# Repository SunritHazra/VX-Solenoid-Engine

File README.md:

# VX Solenoid Engine — V2 Solenoid Engine

The project *"V2 Solenoid Engine"* is the second project of the long-term vision of "VX Solenoid Engine", which aims to build progressive solenoid engines with real engineering and proper planning. I have designed and completed the V1 Solenoid Engine before which was the prototype (you can find this in the first journal entry), and I had a partially designed a V10 Solenoid Engine with the help of an engineer from the United Kingdom (UK).

The V2 Solenoid Engine is a custom-designed electromechanical engine that converts electrical energy into rotational mechanical motion using electromagnetic actuation. Instead of combustion, the engine uses solenoids to generate magnetic fields that pull ferromagnetic plungers inside cylindrical sleeves, producing linear motion. This motion is transferred through a yoke and crankshaft mechanism that converts the linear movement into continuous rotation, similar to the working principle of a traditional piston engine.

This project is made with the aim of creating an engine that works efficiently, consistently and with coolness (not talking about thermal coolness), wirelessly. The ESP32 allows the user to run the engine at any speed, control the firing, etcetera. The engine is intended to be controllable through a laptop, a phone or any device wirelessly.

<center>
  
</center>

We can often see solenoid engines nowadays as hobby toys, on platforms like YouTube, so what separates this project from those?  
Well, this has a PCB, MOSFET switching based on IR sensors, and it is made with performance and efficiency in mind. Please note that, efficiency is not the goal of this project, and this is an experimental setup to study electromagnetic actuation.

---

## Project Overview

The entire mechanical system is designed in **Autodesk Fusion** and the PCBA was designed in **KiCad**, with structural components and mechanical components (except flywheel) intended for MJF and SLS 3D printing, while control electronics are built around an ESP32-DEVKIT-V1 featuring ESP32-WROOM-32 and TCRT5000 IR position sensing. The engine is powered by a Mean Well LRS-450-24, that gives an output of 24 volts and 18.8 amperes.

The current design features a two-cylinder (V2) configuration sharing a single crankshaft, firing at 180 degrees, which improves rotational balance and reduces dead zones during operation. To control the engine’s timing, infrared reflective sensors monitor the position of the crankshaft and provide feedback to an ESP32 microcontroller, which determines when each solenoid should be energized (when the power should be on). A custom PCB handles the electronics (except the SMPS) required for switching the high-current solenoid coils, integrating MOSFET drivers, power regulation, and sensor interfaces while separating high-power and low-voltage logic systems for stability.

The PCB has two different power inputs: one inputs 5V from a battery and one inputs 24V from the Mean Well LRS-450-24 (18.8 A). There are four more logical inputs (screw terminals): Two (4 pins) for each of the IR Sensor, for A, CATH, COLL and E. And there are two big output screw terminals, for each solenoid.

The PCB has no traces for the components through which 18.8 A flows. So, they have to be soldered pin-to-pin manually with thick wire suitable for that current like 18 AWG. I did this as I didn't want to make the traces too thick, probable to overheating and for safety reasons. And of course, I didn't want to use 2 oz thickness as it is expensive.

Together, the mechanical structure, sensing system, embedded controller, and power electronics form a programmable electromagnetic engine platform that allows experimentation with firing timing, control strategies, and electromechanical system design.

The engine demonstrates:
* Electromagnetic actuation
* Crankshaft-based mechanical power conversion
* Embedded timing control
* Hybrid manufacturing (3D printing + CNC)
* MOSFET Switching

**Note:** The flywheel has to be as heavy as possible, so it is better to CNC machine it despite the cost. A large flywheel is used to stabilize rotational inertia and maintain smooth motion between electromagnetic pulses.

---

## Core Concept

A solenoid is an electromechanical device that generates a magnetic field when current flows through its copper coil. A ferromagnetic plunger inside the solenoid is pulled toward the coil center. I just doubled it so that it looks more cool, and is more loud (really).

In this engine, this is what happens fundamentally:
1. A microcontroller (ESP32) activates the solenoid coil based on the position of the crank
2. Magnetic force pulls the ferromagnetic soft iron plunger
3. The plunger drives the connecting rod connected to the crankshaft
4. The crankshaft rotates
5. A flywheel smooths rotational motion
6. IR sensors detect crank position
7. The controller switches coils again

This cycle produces **continuous rotation**, with two pistons firing periodically at 180 degrees.

---

## Key Features

### Multi-Cylinder Mechanical Layout
The engine uses a **V2 configuration**, where two solenoid-driven cylinders operate on a shared crankshaft. This arrangement improves balance and reduces rotational dead zones, allowing smoother and more continuous motion.

### Electromagnetic Actuation
Each cylinder converts electrical energy into linear mechanical motion.  
Each cylinder contains:
* Copper coil winding
* Ferromagnetic plunger
* Linear motion sleeve

When current flows through the coil, a magnetic field is generated that pulls the plunger inward. The plunger’s movement converts magnetic attraction into controlled mechanical displacement.

### Crankshaft Mechanism
The crankshaft converts the linear motion of the plungers into rotational motion.  
Main components include:
* Crank pins
* Yokes
* Connecting linkages

The crankshaft geometry is intentionally compact and shortened to reduce friction losses and improve overall mechanical efficiency.

### Flywheel Stabilization
A large flywheel is mounted on the crankshaft to stabilize rotation.  
Its functions include:
* Increasing rotational inertia
* Reducing stalling between solenoid pulses
* Smoothing torque output

The flywheel helps maintain continuous rotation even when the solenoids are not actively pulling the plungers.

### Optical Position Sensing
The engine uses TCRT5000 infrared reflective sensors to detect crankshaft position.  
These sensors allow the control system to:
* Identify the rotational phase of the crankshaft
* Trigger solenoids at the correct timing
* Prevent mistimed coil activation

This sensing system transforms the engine from a passive mechanism into an actively controlled electromechanical system.

### Exoskeleton Structural Frame
The engine is supported by a rigid exoskeleton frame that holds the mechanical system together. The frame:
* Maintains alignment of cylinders
* Supports bearings and shaft components
* Prevents structural flexing
* Provides mounting points for sensors and electronics

The exoskeleton also allows modular modifications and easier maintenance.

---

## Mechanical Design

The mechanical system consists of several interacting components that convert electromagnetic actuation into rotational motion.

**Solenoid Cylinder Assembly**  
Each cylinder assembly contains:
* Coil housing
* Copper winding space
* Plunger sleeve
* Linear motion channel

The sleeve guides the plunger along a fixed path and ensures proper alignment during motion.

**Yoke Mechanism**  
The yoke connects the plunger to the crankshaft and transfers the linear motion.  
The yoke geometry was thickened to:
* Increase structural strength
* Provide sufficient space for coil windings
* Reduce mechanical deformation during operation

**Crankshaft**  
The crankshaft assembly includes:
* Crank throws
* Bearing supports
* Shaft core
* Flywheel mount

The crank geometry was designed to minimize rotational inertia and reduce mechanical drag.

**Structural Frame**  
The outer frame forms a rigid skeleton that supports the entire mechanical system.  
It provides mounting locations for:
* Cylinder assemblies
* Sensor placements
* Bearing supports
* Crankshaft alignment

---

## Electronics Architecture

The electronics system coordinates solenoid activation and processes sensor input.

**Microcontroller**  
The engine uses an ESP32 DevKit V1 microcontroller.  
Responsibilities include:
* Reading sensor signals
* Determining crankshaft position
* Controlling solenoid activation timing
* Executing control logic

The microcontroller also enables future expansions such as telemetry and advanced control algorithms.

**Position Sensors**  
Crankshaft position is detected using TCRT5000 IR reflective sensors.  
These sensors detect reflective markers attached to the rotating assembly and provide feedback necessary for correct timing of solenoid activation.

**Power System**  
The solenoid coils require high-current switching.  
The typical power architecture includes:
* 24 V power supply
* MOSFET switching stage
* Flyback protection diodes
* Capacitor banks for current stabilization

These components allow safe and efficient control of the solenoid currents.

---

## Manufacturing Plan

The project uses a hybrid fabrication approach, combining additive manufacturing with CNC machining, to balance cost and quality.

**3D Printed Components**  
Most structural components are designed for 3D printing, including:
* Engine frame
* Coil housings
* Yokes
* Sensor mounts
* Structural supports

Likely materials include:
* PLA for early prototyping
* PETG or ABS for stronger functional parts

**CNC Machined Components**  
Precision mechanical parts are planned to be manufactured using CNC machining, primarily through JLCMC.  
These parts include:
* Crankshaft
* Metal shafts
* Mechanical fasteners
* Possibly the flywheel

CNC machining provides better tolerances, strength, and durability for rotating components.

---

## Bill of Materials

A complete bill of materials is provided in **BOM.csv**.  
**Note:** Cart screenshots for Amazon, JLC, and Robu have been added in the design review already. Certain parts are sourced locally and paid for by the creator. Therefore, it is not possible to provide links for those items, and their costs are not included in the BOM requested from HCB.

---

## Firmware

Firmware source code is located at:  
**Firmware/V2 Solenoid Engine Firmware.cpp**

To flash the firmware:
1. Install the Arduino IDE.
2. Install the ESP32 board package.
3. Open the firmware file.
4. Select the correct ESP32 board and port.
5. Upload the firmware to the microcontroller.

After flashing, disconnect USB if powering externally.  
(For PlatformIO users: platformio.ini is included in the firmware folder.)

---

## Wiring

The full wiring schematic is provided here:  
**Media/V2 Solenoid Engine Schematic and Wiring.pdf**

**External Wiring Summary**  
Mean Well LRS-450-24 (+24V/GND) ─── 18 AWG Red/Black ─── J1 on PCB  
Solenoid + connected to +24V rail  
Solenoid - connected to MOSFET drains (manual 18 AWG)  
TCRT5000 sensors connected to their 4-pin headers (A, CATH, COLL, E) → GPIO34/35  
NTC thermistor connected to GPIO36  

**One very important note (again):** The PCB has no traces for the components through which 18.8 A flows. So, they have to be soldered pin-to-pin manually with thick wire suitable for that current like 18 AWG. I did this as I didn't want to make the traces too thick, probable to overheating and for safety reasons. And of course, I didn't want to use 2 oz thickness as it is expensive.

---

## Assembly and Operation Guide

This guide explains how to assemble, wire, and operate the V2 Solenoid Engine after printing the mechanical parts and manufacturing the PCB. Read the entire document before starting assembly.  
Please note that this guide is not completely reliable as the engine is not manufactured and assembled (as of March, 2026).

**Safety Information**  
This project uses 24V DC power, 18.8 A and contains fast moving mechanical parts.  
Follow these obvious precautions:  
- Never power the system while assembling the mechanical structure.  
- Keep fingers, hair, and loose clothing away from the crankshaft and flywheel while running.  
- Always use a regulated 24V power supply capable of supplying adequate current.  
- Ensure correct polarity when connecting the power supply.  
- Disconnect power immediately if components become excessively hot or behave unexpectedly.  
- Do not run the engine unattended.

**Required Components**  
All required components are listed in the Bill of Materials:  
**Bill of Materials/V2 Bill of Materials.csv**

**Tools Required**  
Typical tools required for assembly include:  
- Hex keys / Allen keys  
- Screwdrivers  
- Small wrench or socket set  
- Soldering iron (if assembling PCB manually)  
- Wire cutters and strippers  
- Threadlocker (recommended for high-vibration components)

**Mechanical Assembly**  
Follow these general steps to assemble the mechanical structure.  
#### 1. Frame Assembly  
- Assemble the main frame using the 3D printed structural parts.  
- Secure all frame pieces using the specified fasteners from the BOM.  
- Ensure the frame is rigid and square.  

#### 2. Crankshaft and Flywheel  
- Install the crankshaft into the frame supports.  
- Attach the flywheel to the crankshaft.  
- Verify that the shaft rotates freely with minimal friction.  

#### 3. Piston and Connecting Rod  
- Attach the connecting rod to the crankshaft.  
- Install the piston assembly.  
- Ensure the piston moves smoothly through its full range of motion.  

#### 4. Solenoid Mounting  
- Mount the solenoid in the designated bracket.  
- Align the solenoid plunger with the piston linkage.  
- Ensure the plunger moves freely and does not bind.  

#### 5. Final Mechanical Check  
- Rotate the crankshaft manually.  
- Confirm the full mechanism moves smoothly.  
- Verify that no parts collide or rub excessively.  

**PCB Installation**  
The PCB design files are located in:  
**PCBA/**  
Files included:  
- KiCad project  
- PCB layout  
- schematic  
- gerbers  
- STEP model  

**PCB Mounting**  
- Secure the PCB to the frame using the provided mounting holes.  
- Ensure the board is isolated from metal surfaces if necessary.  
- Maintain airflow around the board for cooling.  

---

## Operation

After the engine is fully assembled and wired:  
1. Ensure the crankshaft rotates freely.  
2. Verify all wiring connections.  
3. Connect the 24V power supply.  
4. Power the system.  

The firmware will drive the solenoid according to the programmed timing, causing the piston to actuate and rotate the crankshaft.  
The flywheel stabilizes the rotation and maintains momentum between solenoid pulses.

---

## Expected Behavior

When operating correctly:  
- The engine should begin rotating shortly after power is applied.  
- The flywheel should maintain smooth rotational motion.  
- The solenoid should actuate in synchronization with the crankshaft motion.  

Performance depends on:  
- Supply voltage stability  
- Mechanical friction  
- Solenoid characteristics  
- Firmware timing parameters  

---

## Troubleshooting

If the engine does not operate correctly:  

**Engine does not start**  
- Verify 24V power supply is connected.  
- Confirm correct wiring according to the schematic.  
- Ensure firmware was successfully flashed.  

**Solenoid does not activate**  
- Check PCB connections.  
- Verify the solenoid wiring.  
- Confirm correct ESP32 operation.  

**Engine stalls or runs poorly**  
- Inspect mechanical alignment.  
- Check for excessive friction.  
- Ensure solenoid plunger moves freely.  

**Excessive heat**  
- Disconnect power immediately.  
- Inspect wiring and current draw.  
- Verify the solenoid is not being continuously energized.  

---

## Additional Files

Relevant files in the repository:  
- **CAD/V2 Solenoid Engine v10.f3d** — Fusion 360 source model  
- **CAD/V2 Solenoid Engine v10.step** — universal 3D model  
- **PCBA/** — PCB design and manufacturing files  
- **Bill of Materials/V2 Bill of Materials.csv** — full component list  
- **Media/** — renders, PCB images, and wiring diagram  
- **Firmware/V2 Solenoid Engine Firmware.cpp** — ESP32 firmware (untested though)  

---

## Final Notes

Before operating the engine for extended periods, perform several short test runs to ensure mechanical stability and safe electrical behavior, because you are basically playing with 18.8 amperes and 24 volts, just for fun (maybe).  
Regularly inspect fasteners, moving components, and electrical connections to maintain safe operation, cause the thing vibrates, A LOT!
By the way, the safety guidelines are written based on real experience when the V1 Solenoid Engine was built.

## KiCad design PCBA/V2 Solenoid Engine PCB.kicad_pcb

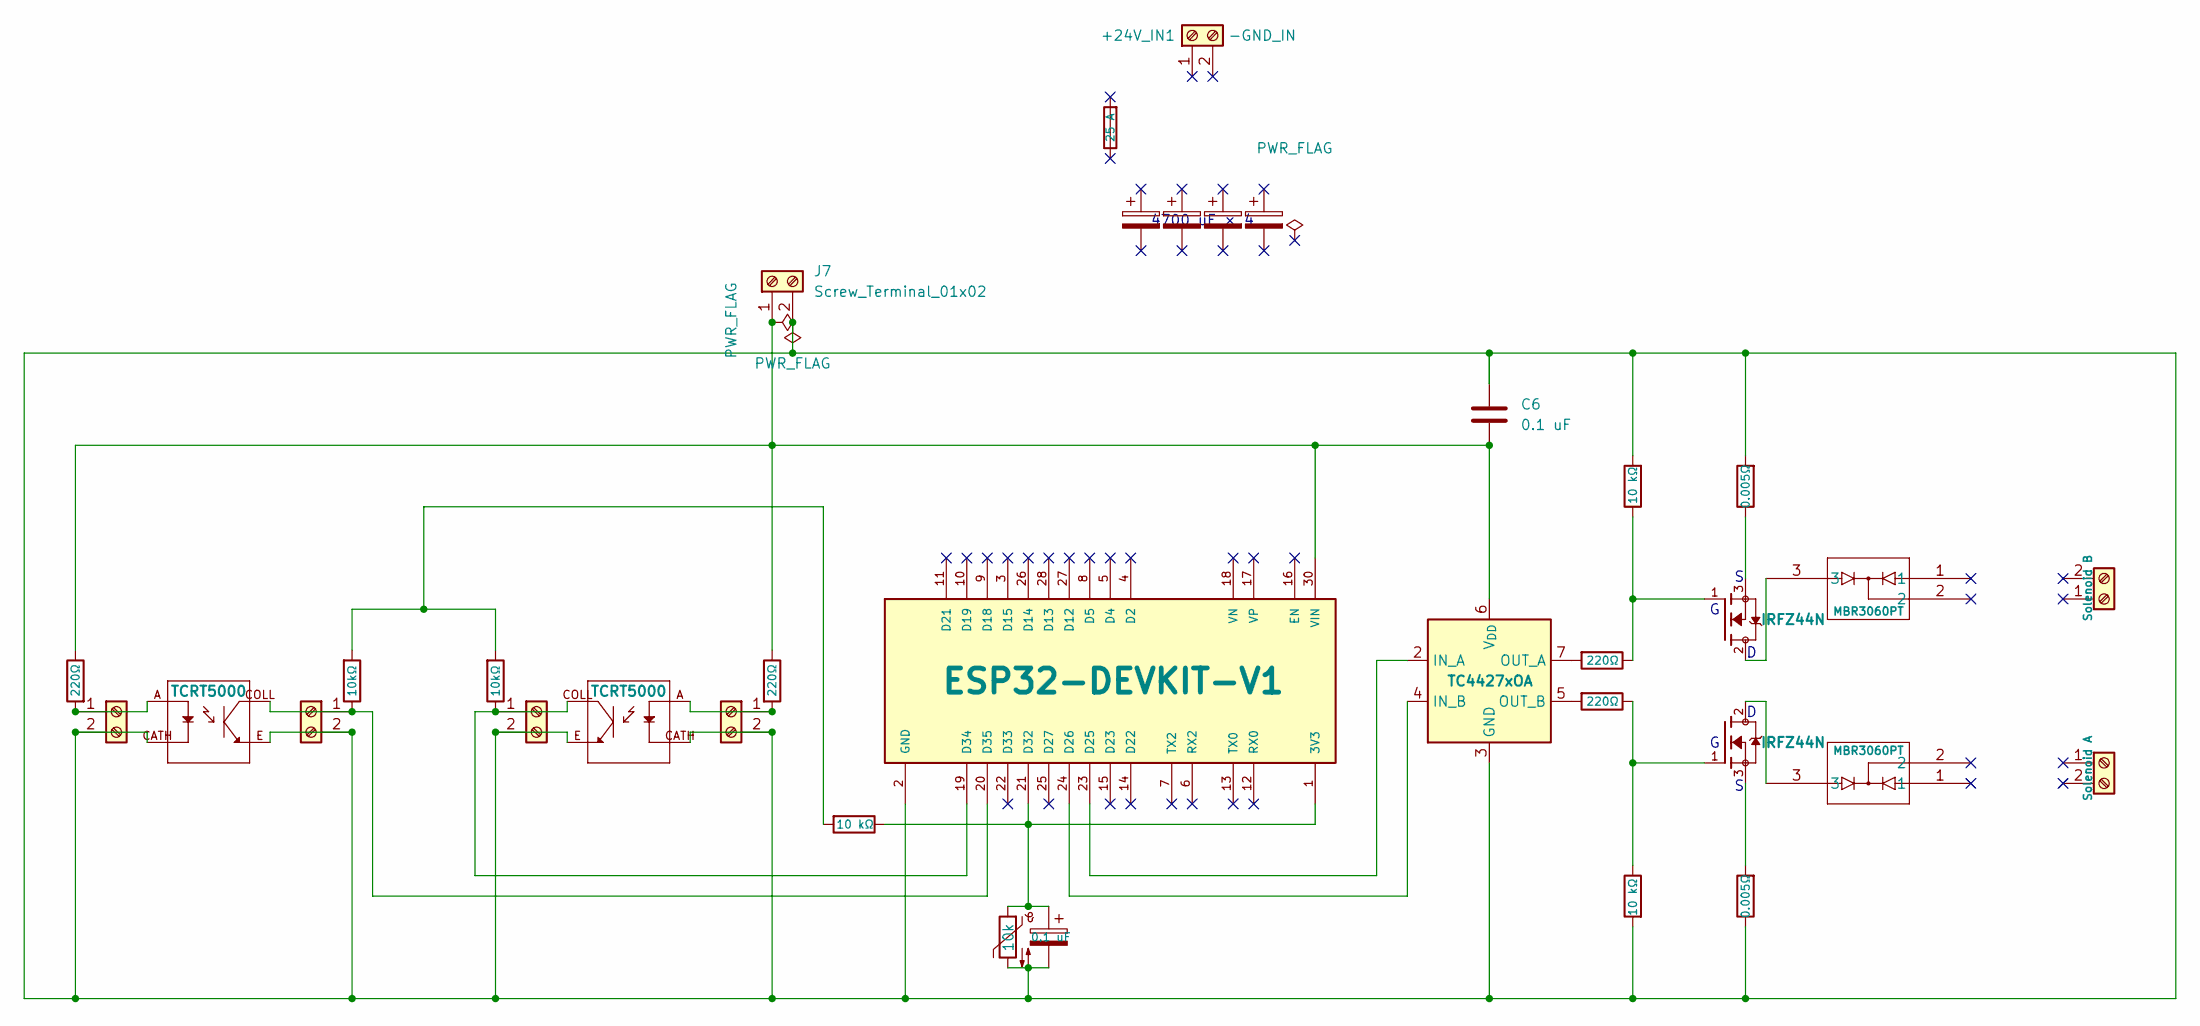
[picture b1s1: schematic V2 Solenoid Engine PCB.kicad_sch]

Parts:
+24V_IN1: -GND_IN; TerminalBlock_Phoenix_PT-1,5-2-5.0-H_1x02_P5.00mm_Horizontal
C1, C2, C3, C4: C_Polarized; CP_Radial_D16.0mm_P7.50mm
C5, C6: 0.1 uF; C_0805_2012Metric
CR1, CR2: MBR3060PT; TO-247-3LD_340CC_ONS
F1: 25 A; Fuseholder_Cylinder-5x20mm_Schurter_0031_8201_Horizontal_Op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
J1, J2, J3, J4: Screw_Terminal_01x02; TerminalBlock_Phoenix_MKDS-1,5-2_1x02_P5.00mm_Horizontal
J5: Solenoid B; TerminalBlock_Ningbo-Kagnex_HB9500M_1x02_P9.5mm
J6: Solenoid A; TerminalBlock_Ningbo-Kagnex_HB9500M_1x02_P9.5mm
J7: Screw_Terminal_01x02; TerminalBlock_Phoenix_PT-1,5-2-5.0-H_1x02_P5.00mm_Horizontal
Q1, Q2: IRFZ44N; TO-220-3_Vertical; PARTREV 09/21/10
R1, R2, R8, R11: 220Ω; R_Axial_DIN0207_L6.3mm_D2.5mm_P7.62mm_Horizontal
R3, R5, R7: 10 kΩ; R_Axial_DIN0207_L6.3mm_D2.5mm_P7.62mm_Horizontal
R4, R6: 0.005Ω; R_2512_6332Metric
R9, R10: 10kΩ; R_Axial_DIN0207_L6.3mm_D2.5mm_P7.62mm_Horizontal
TH1: 10k; R_Axial_DIN0207_L6.3mm_D2.5mm_P7.62mm_Horizontal
U1: ESP32-DEVKIT-V1; MODULE_ESP32_DEVKIT_V1; PARTREV N/A
U2: TC4427xOA; SOIC-8_3.9x4.9mm_P1.27mm
U5, U6: TCRT5000; Vishay_TCRT5000; PARTREV 1.7

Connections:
GND: C5.2, C6.1, J1.2, J2.2, J3.2, J4.2, J7.2, R3.2, R4.2, R5.2, R6.1, TH1.2, U1.2 (GND), U1.29 (GND), U2.3 (GND), U5.CATH, U5.E, U6.CATH, U6.E
unnamed: CR1.3, Q2.2
unnamed: CR2.3, Q1.2
unnamed: J1.1, R8.2, U6.A
unnamed: J2.1, R9.1, U1.19 (D34), U6.COLL
unnamed: J3.1, R11.2, U5.A
unnamed: J4.1, R10.1, U1.20 (D35), U5.COLL
unnamed: C6.2, J7.1, R8.1, R11.1, U1.30 (VIN), U2.6 (V_{DD})
unnamed: Q1.1, R1.1, R3.1
unnamed: Q1.3, R4.1
unnamed: Q2.1, R2.1, R5.1
unnamed: Q2.3, R6.2
unnamed: R7.2, R9.2, R10.2
unnamed: C5.1, R7.1, TH1.1, U1.1 (3V3), U1.21 (D32)
unnamed: U1.23 (D25), U2.2 (IN_A)
unnamed: U1.24 (D26), U2.4 (IN_B)
unnamed: R1.2, U2.7 (OUT_A)
unnamed: R2.2, U2.5 (OUT_B)

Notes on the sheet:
4700 uF × 4

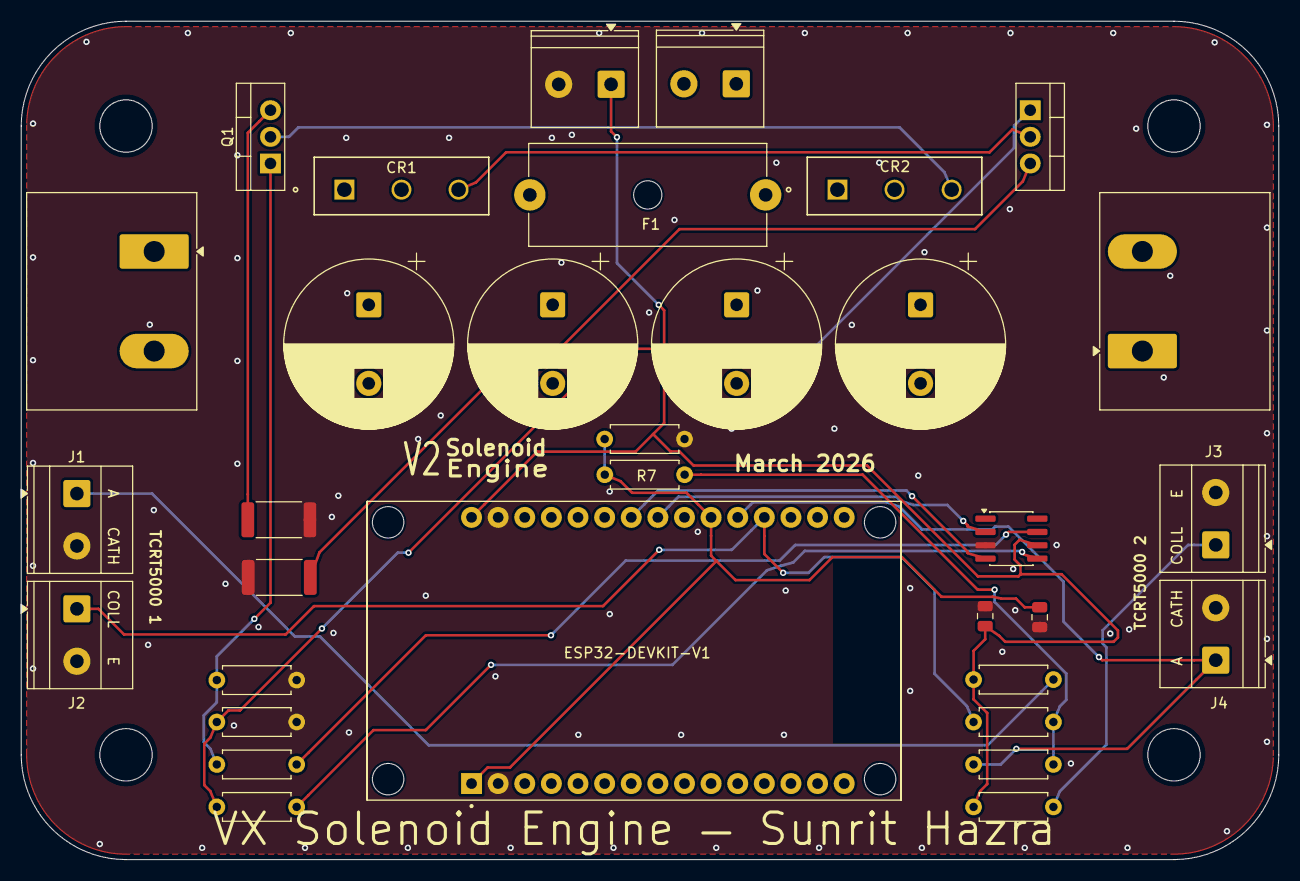
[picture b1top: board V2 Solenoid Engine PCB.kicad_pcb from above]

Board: 2 copper layers, 120.0 x 80.0 mm, 33 parts (0 on the bottom side), 18 nets.

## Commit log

2026-03-08 Rename vx-solenoid-engine-journal.md to VX-Solenoid-Engine-Journal.md
2026-03-27 Rename V2 Bill of Materials.csv to V2 Solenoid Engine — Bill of Materials.csv
2026-03-27 Rename Bill of Materials.md to V2 Solenoid Engine — Bill of Materials.md
2026-04-03 Rename V2 Solenoid Engine — Bill of Materials.csv to V2 Solenoid Engine — Bill of Materials [ORIGINAL].csv
    This is the original CSV submitted for grant request for Blueprint YSWS by Hack Club
2026-05-29 Rename VX-Solenoid-Engine-Journal.md to V2-Solenoid-Engine-Journal.md
